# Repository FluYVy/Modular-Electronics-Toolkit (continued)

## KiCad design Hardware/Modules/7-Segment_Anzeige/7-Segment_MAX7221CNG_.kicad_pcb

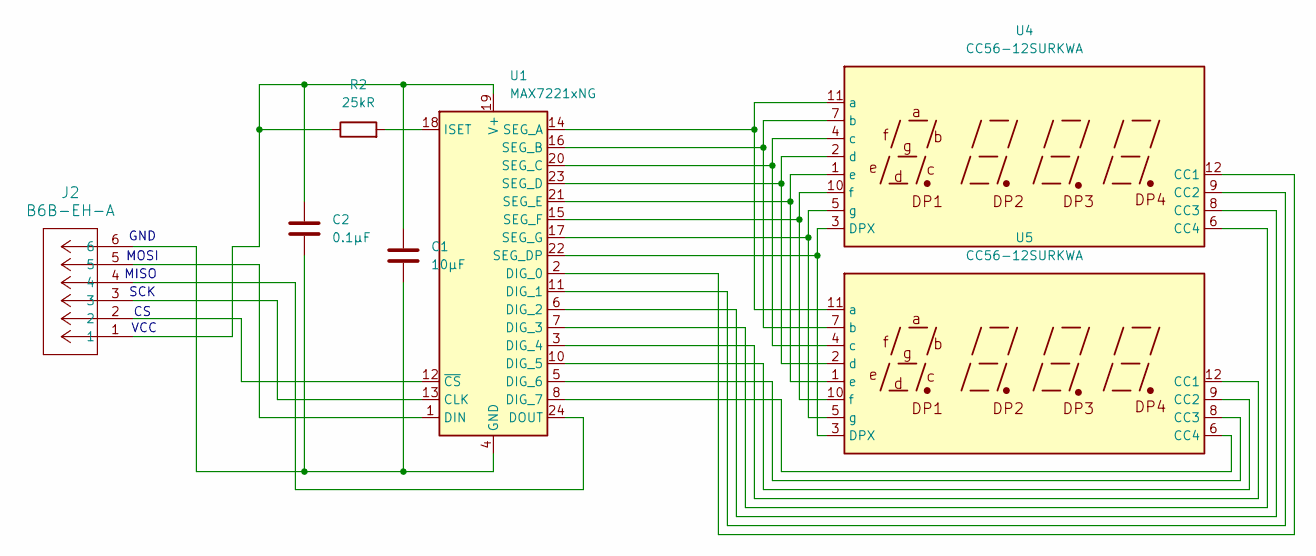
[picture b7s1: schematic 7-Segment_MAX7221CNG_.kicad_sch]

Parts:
C1: 10µF; C_Elec_3x5.4
C2: 0.1µF; C_0603_1608Metric_Pad1.08x0.95mm_HandSolder
J2: B6B-EH-A; JST_EH_B6B-EH-A_1x06_P2.50mm_Vertical
R2: 25kR; R_0603_1608Metric_Pad0.98x0.95mm_HandSolder
U1: MAX7221xNG; DIP-24_W7.62mm
U4, U5: CC56-12SURKWA; CA56-12SURKWA_autorouting

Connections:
unnamed: C1.2, C2.2, J2.6, U1.4 (GND), U1.9 (GND)
unnamed: J2.3, U1.13 (CLK)
unnamed: U1.2 (DIG_0), U4.12 (CC1)
unnamed: U1.11 (DIG_1), U4.9 (CC2)
unnamed: U1.6 (DIG_2), U4.8 (CC3)
unnamed: U1.7 (DIG_3), U4.6 (CC4)
unnamed: U1.3 (DIG_4), U5.12 (CC1)
unnamed: U1.10 (DIG_5), U5.9 (CC2)
unnamed: U1.5 (DIG_6), U5.8 (CC3)
unnamed: U1.8 (DIG_7), U5.6 (CC4)
unnamed: J2.5, U1.1 (DIN)
unnamed: J2.4, U1.24 (DOUT)
unnamed: R2.2, U1.18 (ISET)
unnamed: U1.14 (SEG_A), U4.11 (a), U5.11 (a)
unnamed: U1.16 (SEG_B), U4.7 (b), U5.7 (b)
unnamed: U1.20 (SEG_C), U4.4 (c), U5.4 (c)
unnamed: U1.23 (SEG_D), U4.2 (d), U5.2 (d)
unnamed: U1.22 (SEG_DP), U4.3 (DPX), U5.3 (DPX)
unnamed: U1.21 (SEG_E), U4.1 (e), U5.1 (e)
unnamed: U1.15 (SEG_F), U4.10 (f), U5.10 (f)
unnamed: U1.17 (SEG_G), U4.5 (g), U5.5 (g)
unnamed: C1.1, C2.1, J2.1, R2.1, U1.19 (V+)
unnamed: J2.2, U1.12 (~CS)

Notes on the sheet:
SCK
VCC
GND
MOSI
MISO

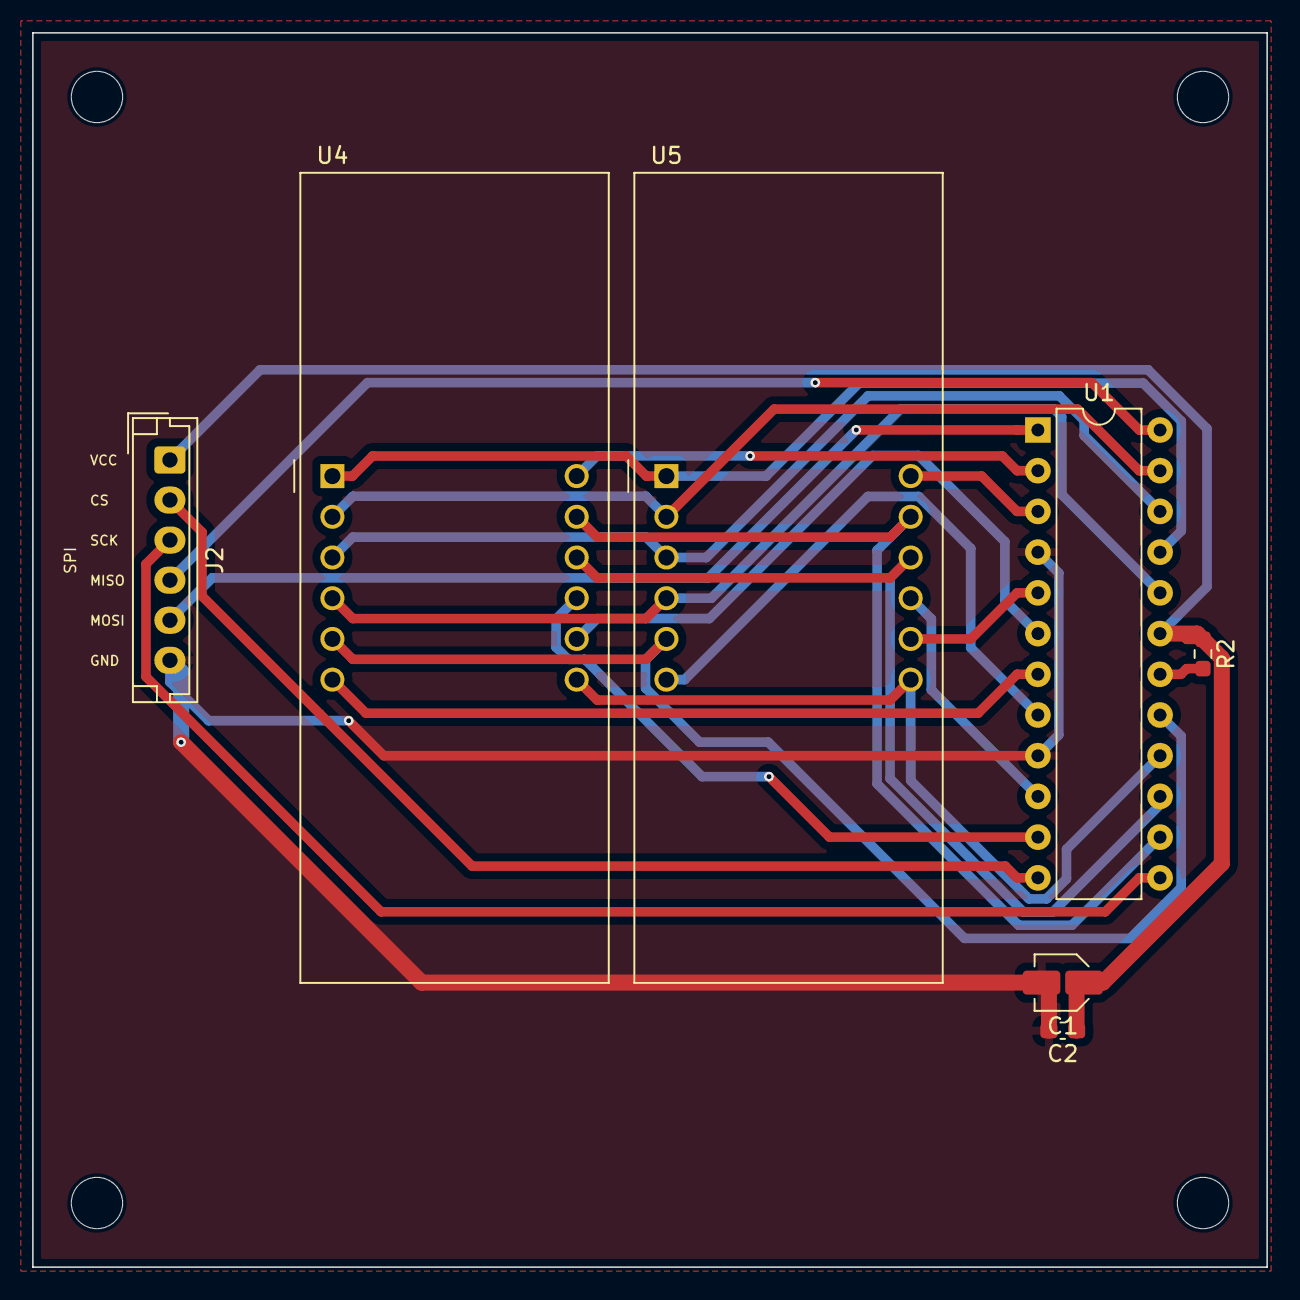
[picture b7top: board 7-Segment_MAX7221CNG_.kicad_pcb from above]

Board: 2 copper layers, 77.0 x 77.0 mm, 11 parts (0 on the bottom side), 23 nets.

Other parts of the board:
H1, H2, H3, H4: MountingHole_3.2mm_M3

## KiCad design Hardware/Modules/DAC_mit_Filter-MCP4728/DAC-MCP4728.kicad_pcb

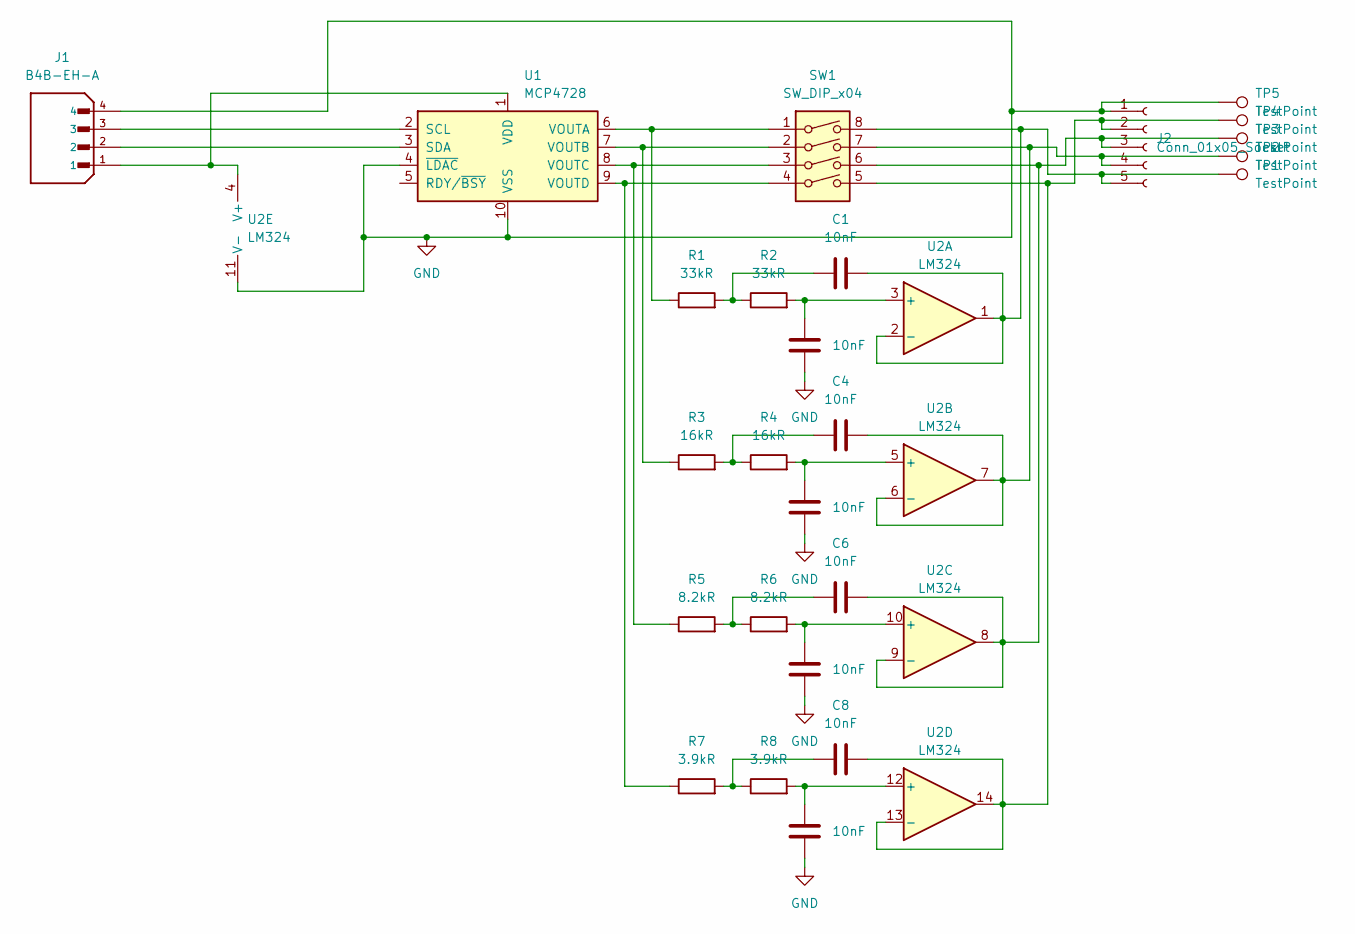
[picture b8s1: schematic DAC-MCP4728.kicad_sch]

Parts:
C1, C2, C3, C4, C5, C6, C7, C8: 10nF; C_0603_1608Metric_Pad1.08x0.95mm_HandSolder
J1: B4B-EH-A; JST_EH_B4B-EH-A_1x04_P2.50mm_Vertical
J2: Conn_01x05_Socket; PinSocket_1x05_P2.54mm_Vertical
R1, R2: 33kR; R_0603_1608Metric_Pad0.98x0.95mm_HandSolder
R3, R4: 16kR; R_0603_1608Metric_Pad0.98x0.95mm_HandSolder
R5, R6: 8.2kR; R_0603_1608Metric_Pad0.98x0.95mm_HandSolder
R7, R8: 3.9kR; R_0603_1608Metric_Pad0.98x0.95mm_HandSolder
SW1: SW_DIP_x04; SW_DIP_SPSTx04_Slide_9.78x12.34mm_W7.62mm_P2.54mm
TP1, TP2, TP3, TP4, TP5: TestPoint; TestPoint_Pad_1.0x1.0mm
U1: MCP4728; TSSOP-10_3x3mm_P0.5mm
U2: LM324; SOIC-14_3.9x8.7mm_P1.27mm

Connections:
GND: C2.2, C3.2, C5.2, C7.2, J1.4, J2.1, TP5.1, U1.4 (~LDAC), U1.10 (VSS), U2.11 (V-)
unnamed: C1.1, R1.2, R2.1
unnamed: C4.1, R3.2, R4.1
unnamed: C6.1, R5.2, R6.1
unnamed: C8.1, R7.2, R8.1
unnamed: C8.2, J2.2, SW1.5, TP4.1, U2.13 (-), U2.14
unnamed: C6.2, J2.3, SW1.6, TP3.1, U2.8, U2.9 (-)
unnamed: C4.2, J2.4, SW1.7, TP2.1, U2.6 (-), U2.7
unnamed: C1.2, J2.5, SW1.8, TP1.1, U2.1, U2.2 (-)
unnamed: J1.3, U1.2 (SCL)
unnamed: J1.2, U1.3 (SDA)
unnamed: J1.1, U1.1 (VDD), U2.4 (V+)
unnamed: R1.1, SW1.1, U1.6 (VOUTA)
unnamed: R3.1, SW1.2, U1.7 (VOUTB)
unnamed: R5.1, SW1.3, U1.8 (VOUTC)
unnamed: R7.1, SW1.4, U1.9 (VOUTD)
unnamed: C2.1, R2.2, U2.3 (+)
unnamed: C3.1, R4.2, U2.5 (+)
unnamed: C5.1, R6.2, U2.10 (+)
unnamed: C7.1, R8.2, U2.12 (+)

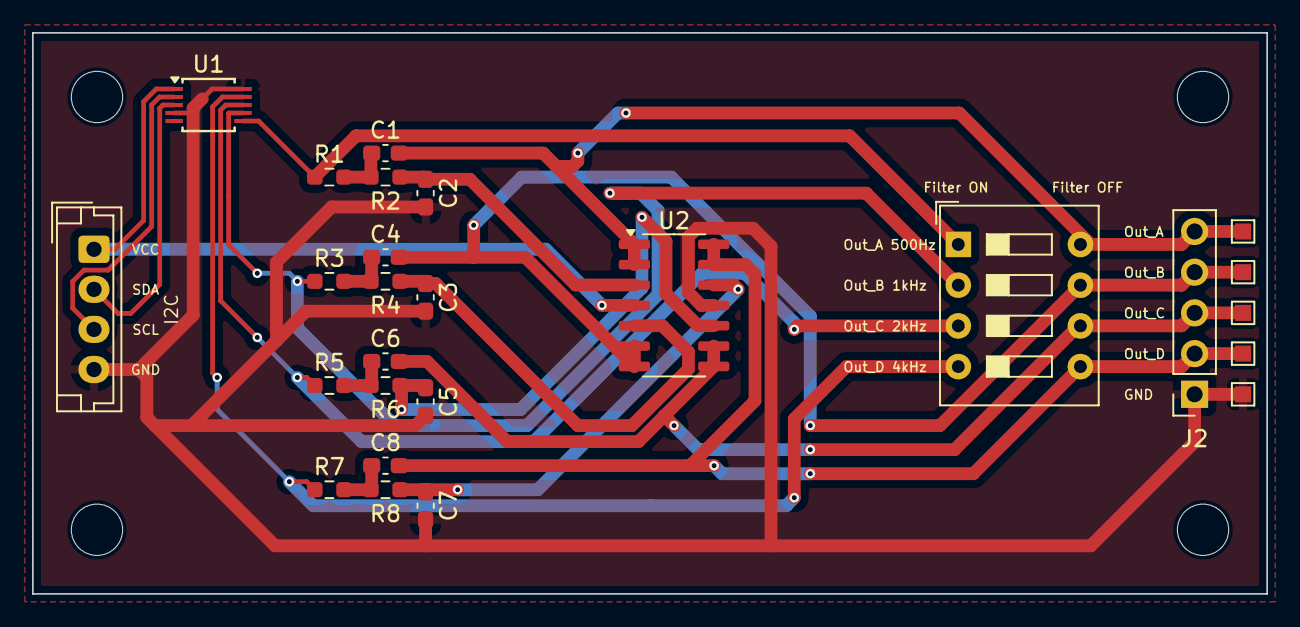
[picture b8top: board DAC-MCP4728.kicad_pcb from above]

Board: 2 copper layers, 77.0 x 35.0 mm, 30 parts (0 on the bottom side), 20 nets.

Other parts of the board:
H1, H2, H3, H4: MountingHole_3.2mm_M3

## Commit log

2024-07-20 Create .gitignore for Library-Development
2024-08-15 Edit .gitignore for Library-Development
2024-08-15 Created i2c_master-script
2024-08-15 Created test-script for i2c_master
2024-08-15 Created .gitignore for Hardware
2024-08-15 Created Templates for Hardware
2024-09-01 Edited Templates for Hardware
    Edited size of templates to fit within containers
2024-10-08 Small changes to i2c_master library
    - fixed wrong references of variable i2c_frequency
    - moved includes from .c to .h file
2024-10-08 Created library for SCD41-Sensor
    untested library for SCD41-Sensor
2024-10-08 Moved i2c_master to subfolder
2024-10-08 Create KiCad library
    Contains the "special" components used.
2024-10-14 Heartrate-sens
    This is the Heartrate Sensor...
2024-10-14 More Functions for SCD41-sensor
    - Added other available functions of the SCD41-sensor
    - Created functions to return the measured values
    - get_co2()
    - get_temperature()
    - get_humidity()
2024-10-14 Create basic test for SCD41 sensor
    Added a simple script which reads the values of the SCD41 sensor and displays them on the LEDs.
2024-10-14 Air_Quality_Sens
    This is the Air_Quality Sensor
2024-10-28 Created basic Library for MAX30101 / MAX32664A
    Untested and very basic library for Heartrate and SpO2
2024-10-28 Created basic library for AL5887
    Untested
2024-10-29 Created SPI-Master-Library
    Untestet
2024-10-29 Added comments to libraries
    Libraries:
    - AL5887
    - max30101
    - SCD41
    - i2c_master
    - spi_master
2024-10-30 Reworked SCD41-Library
    - Made functions for sequences
    - write I2C
    - send I2C command
    - read I2C
    - Reworked comments
2024-10-30 Created WS2812B-Library
    Not testet, should work
2024-10-30 Created Basic UART Library
    Untestet
2024-10-31 Testet i2c_master Library
    Testet i2c_master Library via Waveforms and an Analog Discovery 3
2024-11-01 Testet spi_master Library
    Basic Testscript for spi_master Library for Waveforms
2024-11-04 Pixel Matrix
2024-11-04 Updated silkscreen
2024-11-16 Pin 51 gefixt
2024-12-09 HeartRateV2
2024-12-09 7-Segment_Anzeige fertig
2024-12-09 fixed connector orientation
2024-12-09 fixed GND/VCC issue and added filling zone
2024-12-10 Copper Fill fixed
2024-12-11 Created basic library for ICM-20948
    - Added basic functions (some functions are missing)
    - Added Doxygen-style documentation in the header-file
    - Code is currently untested
    - Access to the register values may need to be changed
2024-12-16 initial commit for WebUI
2024-12-16 Add Text to Heart-Rate, finish Flight-ModuleV1
2024-12-21 Reworked SCD41-Library
    Changes:
    - Added better Doxygen comments
    - Reworked function names
2024-12-21 Reworked MAX30101-Library
    Changes:
    - Added better Doxygen comments
2024-12-21 Reworked AL5887-Library
    Changes:
    - Added better Doxygen comments
2024-12-21 Added basic library for BMP390
    Notes:
    - Untested
    - Basic
2024-12-22 Added MAX7221-Library
    Notes:
    - untested
    - documented in Doxygen
2024-12-22 Updated spi_master library
    Updated spi_master library to be able to transfer multiple bytes.
2024-12-22 Deleted WS2812b library
    The speed of the microcontroller is to slow to control the LEDs. This was also tested with assembly.
2025-01-02 Started and finished DAC Module with MCP4728
2025-01-15 Added Filters
    Added Low-Pass Sallen-Key Filters that can be turned on or off using dipswitches. The filters have different cut-off frequencies: 500Hz, 1kHz, 2kHz, 4kHz
2025-02-03 Fixed the code + completed some parts
    The display can now show digits and integer with brightness control and clear all.
2025-02-05 Fixed SPI-Master Library
    Fixed and tested spi-master Library
2025-02-07 Updated SCD41-Library
    Changes:
    - Added prefix scd41_ to functions
    - Added functions for the raw data for humidity and temperature
    - Changed wrong datatype in comments
2025-02-07 Update SCD41.c
    Updated SCD41.c to match SCD41.h
2025-02-07 Fixed functions for int8_t, uint16_t, int16_t and started with float
2025-02-10 fixed the max7221_print_float function
2025-02-11 added print_string + bugfixes
    fixed issue with negative power
    fixed displaying "ERR" for error
    added max7221_print_string + added all letters from a-z
2025-02-12 Changed testscript for i2c_master
    Added comments and changed delay to definition
2025-02-12 Fixes + Cleanup for max7221.c
    Cleaned up code
    Added special chars to max7221.h
    Fixed upper-/lowercase for print_string
    Started demo code in main.c
    added length to print_uint8
    modified all functions to delete all unused rightmost digits
2025-02-13 Finished example code + bugfixes
2025-02-17 Finishing Modules
    Wifi-Module
    Flight-Module
    REPAIR:
    - Heartrate
    - Flight-Module
    - Wifi-Module
2025-02-17 Added capacitors to 7-segment display
2025-02-17 Correction in the Wifi Module
2025-02-17 Forgot the ground surfaces
2025-02-17 Reworkd the MegacardV6 Adapterboard
2025-02-17 Fixed Pixel matrix
2025-02-18 Added ADC mit Filter
2025-03-01 Fixed some issues with max7221.h and made it work without spi_master.h and .c
2025-03-21 Changed SCD41-library
    Changed SCD41-Library for easier use for user.
2025-04-02 Pushing Final Versions of all Modules (2025)
2025-04-04 Added Pixelmatrix
2025-04-04 Finall Version of the Wifi-Module (correct mistakes))
